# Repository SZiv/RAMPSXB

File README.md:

# RAMPSXB
For anyone who does extensive, hardcore, overkill 3D printer work, will typically run out of either stepper motor slots for extruders, MOSFETS for Heaters/fans, or Thermistor pins. The options for this are to either upgrade to an expensive mainboard like a duet, or add on individial drivers for stepper or FET. There isn't really a cheap or easy option. 

Now there is! RAMPSXB is an expansion board for the popular control board RAMPS 1.4 that connects to the AUX and endstop headers like an arduino shield to add functionality to the system. in addition, most components and schematic layouts follow the Reprap Defacto standard, as well as the original RAMPS board, so the thermistors, FETs, microstepping and drivers should all behave as if they were an extension of the RAMPS board itself. Most components are dirt cheap, and the board can be outsourced and assembled with a simple soldering iron. 

RAMPSXB is an expansion board shield for serious 3D printer people that adds an overkill amount of functionality to run high-end extruder systems like the E3D Kraken or Diamond Full Color Hotend: 

- 4 additional Stepper motors (bringing the total to 9; enough to run 6 extruders) 
- 4 additional Thermistor pins
- 4 additional MOSFETs w/ PWM control
- EXP1 and EXP2 headers for a Reprap Full Graphics Smart Controller (With SD Card)
- 4 additional 12V rail pins w/ grounds
- 4 additional 5V rail pins w/ grounds
- 2 steppers have two rows of output pins for driving 2 motors together
- Broken out, preregulated pins for HC-05 Bluetooth Chip
- Isolated input and microcontroller power, so 12V or 24V power can be used for the FETs. 
- Suppression Capacitors on endstops to reduce false positives caused by inductive voltages.
- 1 servo pin (the other 3 were consumed for PWM on the FETs, but are broken out if you want to use them for something other than the FETS)
- Broken out 12C pins 

This comes at the cost of: 
- 3 of the 4 servo pins. 
- Max endstops (there are only min endstops)
- AAAAAAALL the AUX headers (with the exception of 1 digital pin, D40, which is broken out)
- A lot of additional space

If you have questions, feel free to shoot me a message, or if you want to learn more about the making of this project, see here: http://scottziv.com/rampsxb

Be sure to take a look at the Wiki here: http://reprap.org/wiki/RAMPSXB

Happy printing!

Released under GPL V3

# Pin Definitions

E2 Direction      -  15  
E2 Step           -  19  
E2 Enable         -  63  
E3 Direction      -  2  
E3 Step           -  39  
E3 Enable         -  58  
E4 Direction      -  42  
E4 Step           -  44  
E4 Enable         -  43  
E5 Direction      -  32  
E5 Step           -  47  
E5 Enable         -  57  
Thermistor T3     -  A11  
Thermistor T4     -  A12  
Thermistor T5     -  A10  
Thermistor T6     -  A5  
MOSFET H3          -  4  
MOSFET H4          -  5  
MOSFET H5          -  6  
MOSFET H6          -  45    

HC-05 chip, LCD screen, and SD card follow the standard pinouts for the Full Graphic smart controller and RAMPS HC-05 attachment.

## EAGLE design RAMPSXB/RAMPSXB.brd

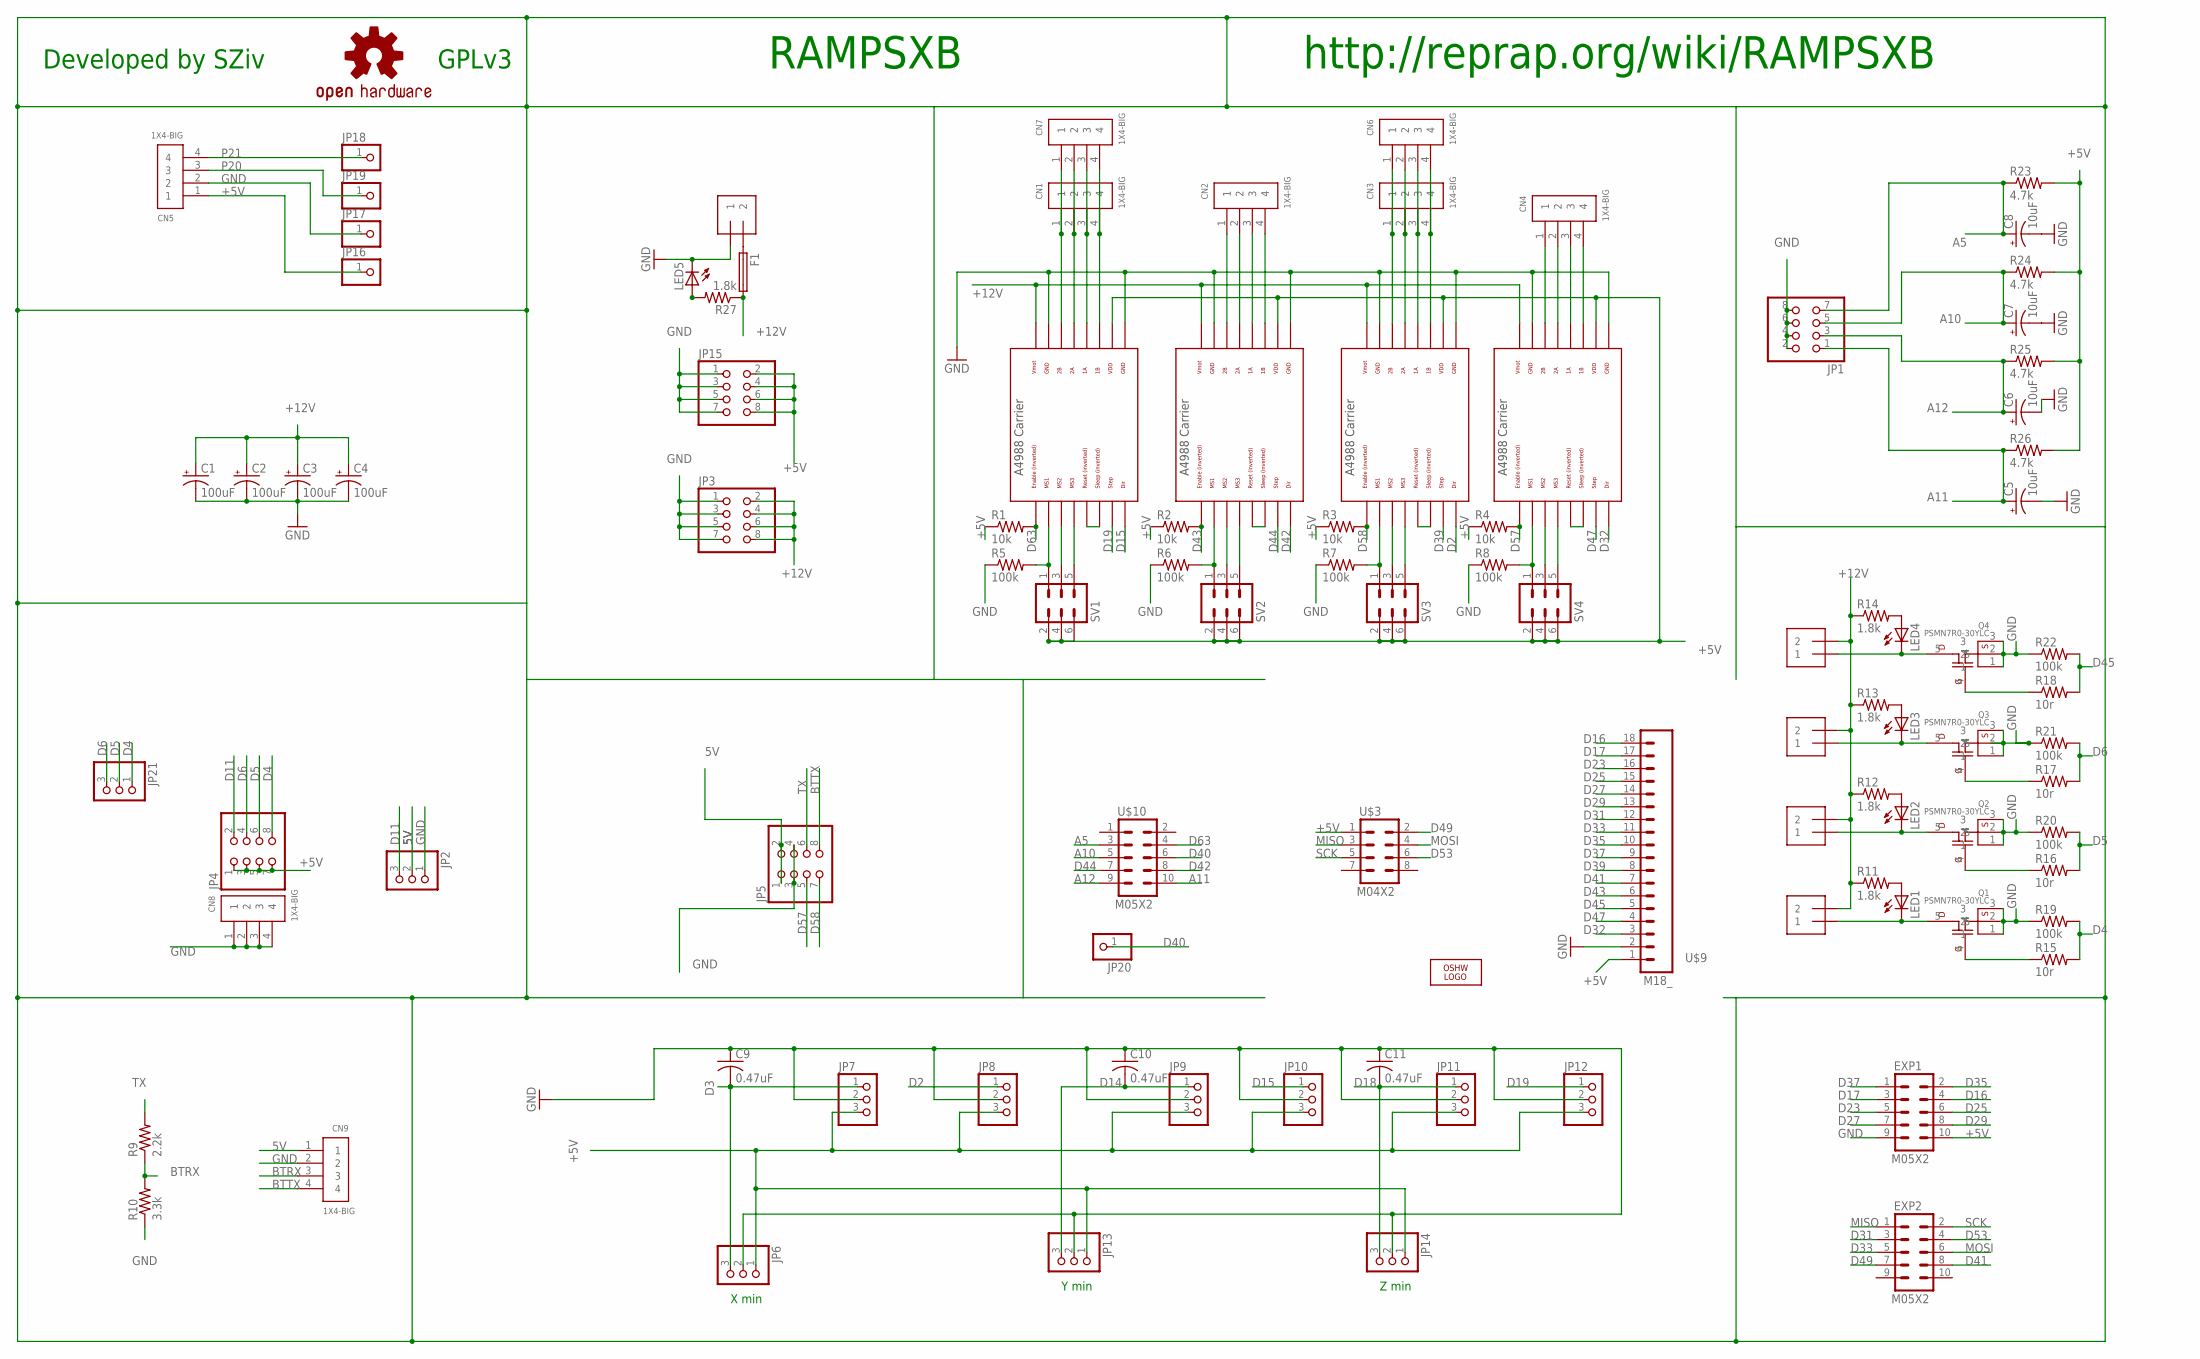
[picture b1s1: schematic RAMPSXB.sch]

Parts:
C1, C2, C3, C4: 100uF; 153CLV-0605
C5, C6, C7, C8: 10uF; 153CLV-0405
C9, C10, C11: 0.47uF; C0805
CN1, CN2, CN3, CN4, CN5, CN6, CN7, CN8, CN9: 1X4-BIG; 1X04-BIG
EXP1, EXP2: M05X2; 2X5
F1: PTCFUSE; LITTLEFUSE
J1, J2, J3, J4, J5: 1X2-3.5MM
JP1, JP3, JP4, JP5, JP15: PINHD-2X4; 2X04
JP2, JP6, JP7, JP8, JP9, JP10, JP11, JP12, JP13, JP14, JP21: PINHD-1X3; 1X03
JP16, JP17, JP18, JP19, JP20: PINHD-1X1; 1X01
LED1, LED2, LED3, LED4, LED5: LEDCHIPLED_0805; CHIPLED_0805
LOGO1: OSHW_LOGO_6MILX0100-NT; OSHW_6X100_NOTEXT
LOGO2: OSHW-LOGOL; OSHW-LOGO-L
Q1, Q2, Q3, Q4: PSMN7R0-30YLC; LFPAK
R1, R2, R3, R4: 10k; M0805
R5, R6, R7, R8, R19, R20, R21, R22: 100k; M0805
R9: 2.2k; M0805
R10: 3.3k; M0805
R11, R12, R13, R14, R27: 1.8k; M0805
R15, R16, R17, R18: 10r; M0805
R23, R24, R25, R26: 4.7k; R0805
SV1, SV2, SV3, SV4: MA03-2
U$1, U$2, U$4, U$5: POLOLU_A4983CARRIER; A4988BREAKOUT
U$3: M04X2; 2X4
U$9: M18_; 1X18
U$10: M05X2; 2X5

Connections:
5V: CN9.1, JP2.2, JP5.1, JP5.2
+5V: CN5.1, EXP1.10, JP4.1, JP4.3, JP4.5, JP4.7, JP6.1, JP7.3, JP8.3, JP9.3, JP10.3, JP11.3, JP12.3, JP13.1, JP14.1, JP15.2, JP15.4, JP15.6, JP15.8, JP16.1, R1.1, R2.1, R3.1, R4.1, R23.2, R24.2, R25.2, R26.2, SV1.2, SV1.4, SV1.6, SV2.2, SV2.4, SV2.6, SV3.2, SV3.4, SV3.6, SV4.2, SV4.4, SV4.6, U$1.VDD, U$2.VDD, U$3.1, U$4.VDD, U$5.VDD, U$9.1
+12V: C1.+, C2.+, C3.+, C4.+, F1.2, J2.2, J3.2, J4.2, J5.2, JP3.2, JP3.4, JP3.6, JP3.8, R11.1, R12.1, R13.1, R14.1, R27.1, U$1.VMOT, U$2.VMOT, U$4.VMOT, U$5.VMOT
A5: C8.+, JP1.7, R23.1, U$10.3
A10: C7.+, JP1.5, R24.1, U$10.5
A11: C5.+, JP1.1, R26.1, U$10.10
A12: C6.+, JP1.3, R25.1, U$10.9
BTRX: CN9.3, R9.1, R10.2
BTTX: CN9.4, JP5.8
D2: JP8.1, U$4.DIR
D3: C9.2, JP6.3, JP7.1
D4: JP4.8, JP21.1, R15.2, R19.2
D5: JP4.6, JP21.2, R16.2, R20.2
D6: JP4.4, JP21.3, R17.2, R21.2
D11: JP2.3, JP4.2
D14: C10.2, JP9.1, JP13.3
D15: JP10.1, U$1.DIR
D16: EXP1.4, U$9.18
D17: EXP1.3, U$9.17
D18: C11.2, JP11.1, JP14.3
D19: JP12.1, U$1.STEP
D23: EXP1.5, U$9.16
D25: EXP1.6, U$9.15
D27: EXP1.7, U$9.14
D29: EXP1.8, U$9.13
D31: EXP2.3, U$9.12
D32: U$5.DIR, U$9.3
D33: EXP2.5, U$9.11
D35: EXP1.2, U$9.10
D37: EXP1.1, U$9.9
D39: U$4.STEP, U$9.8
D40: JP20.1, U$10.6
D41: EXP2.8, U$9.7
D42: U$2.DIR, U$10.8
D43: R2.2, U$2.EN, U$9.6
D44: U$2.STEP, U$10.7
D45: R18.2, R22.2, U$9.5
D47: U$5.STEP, U$9.4
D49: EXP2.7, U$3.2
D53: EXP2.4, U$3.6
D57: JP5.5, R4.2, U$5.EN
D58: JP5.7, R3.2, U$4.EN
D63: R1.2, U$1.EN, U$10.4
GND: C1.-, C2.-, C3.-, C4.-, C5.-, C6.-, C7.-, C8.-, C9.1, C10.1, C11.1, CN5.2, CN8.1, CN8.2, CN8.3, CN8.4, CN9.2, EXP1.9, J1.1, JP1.2, JP1.4, JP1.6, JP1.8, JP2.1, JP3.1, JP3.3, JP3.5, JP3.7, JP5.3, JP5.4, JP6.2, JP7.2, JP8.2, JP9.2, JP10.2, JP11.2, JP12.2, JP13.2, JP14.2, JP15.1, JP15.3, JP15.5, JP15.7, JP17.1, LED5.C, Q1.1, Q1.2, Q1.3, Q2.1, Q2.2, Q2.3, Q3.1, Q3.2, Q3.3, Q4.1, Q4.2, Q4.3, R5.1, R6.1, R7.1, R8.1, R10.1, R19.1, R20.1, R21.1, R22.1, U$1.GND, U$1.GND@0 (GND), U$2.GND, U$2.GND@0 (GND), U$4.GND, U$4.GND@0 (GND), U$5.GND, U$5.GND@0 (GND), U$9.2
MISO: EXP2.1, U$3.3
MOSI: EXP2.6, U$3.4
unnamed: CN1.1, CN7.1, U$1.2B
unnamed: LED5.A, R27.2
unnamed: CN1.3, CN7.3, U$1.1A
unnamed: CN1.4, CN7.4, U$1.1B
unnamed: CN2.1, U$2.2B
unnamed: CN2.2, U$2.2A
unnamed: CN2.3, U$2.1A
unnamed: CN2.4, U$2.1B
unnamed: CN3.1, CN6.1, U$4.2B
unnamed: CN3.2, CN6.2, U$4.2A
unnamed: CN3.3, CN6.3, U$4.1A
unnamed: CN3.4, CN6.4, U$4.1B
unnamed: CN4.1, U$5.2B
unnamed: CN4.2, U$5.2A
unnamed: CN4.3, U$5.1A
unnamed: CN4.4, U$5.1B
unnamed: F1.1, J1.2
unnamed: R5.2, SV1.1, U$1.MS1
unnamed: SV1.3, U$1.MS2
unnamed: SV1.5, U$1.MS3
unnamed: R6.2, SV2.1, U$2.MS1
unnamed: SV2.3, U$2.MS2
unnamed: SV2.5, U$2.MS3
unnamed: R7.2, SV3.1, U$4.MS1
unnamed: SV3.3, U$4.MS2
unnamed: SV3.5, U$4.MS3
unnamed: R8.2, SV4.1, U$5.MS1
unnamed: SV4.3, U$5.MS2
unnamed: SV4.5, U$5.MS3
unnamed: J2.1, LED1.C, Q1.5
unnamed: U$2.RST, U$2.SLP (SLEEP)
unnamed: U$1.RST, U$1.SLP (SLEEP)
unnamed: U$4.RST, U$4.SLP (SLEEP)
unnamed: U$5.RST, U$5.SLP (SLEEP)
unnamed: J3.1, LED2.C, Q2.5
unnamed: J4.1, LED3.C, Q3.5
unnamed: J5.1, LED4.C, Q4.5
unnamed: LED1.A, R11.2
unnamed: LED2.A, R12.2
unnamed: LED3.A, R13.2
unnamed: LED4.A, R14.2
unnamed: CN1.2, CN7.2, U$1.2A
unnamed: Q3.4, R17.1
unnamed: Q4.4, R18.1
unnamed: Q2.4, R16.1
unnamed: Q1.4, R15.1
P20: CN5.3, JP19.1
P21: CN5.4, JP18.1
SCK: EXP2.2, U$3.5
TX: JP5.6, R9.2

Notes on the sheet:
X min
Y min
Z min
RAMPSXB
http://reprap.org/wiki/RAMPSXB
Developed by SZiv
GPLv3

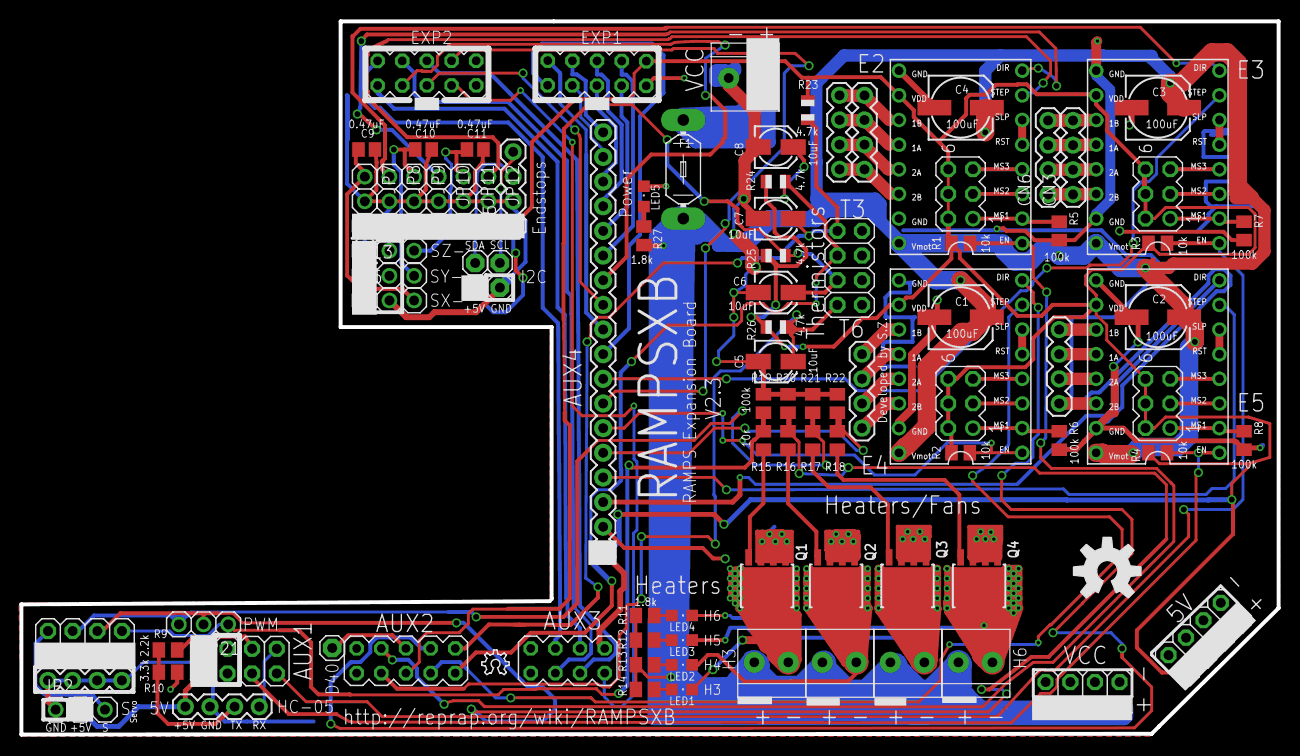
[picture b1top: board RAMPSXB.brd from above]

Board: 2 copper layers, 129.5 x 73.5 mm, 98 parts (0 on the bottom side), 96 nets.

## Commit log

2017-07-25 :boom::camel: Added .gitattributes & .gitignore files
2017-07-25 Main Commit
    First Commit
2017-07-25 Readme Added
    Adding Readme
2017-07-27 V2!
    V2 release. Full PWM, Bluetooth, Larger board.
2017-07-27 Seperated out BOM
2017-08-05 Removed Old RAMPS version.
    SD card slot did not have logic level shifter, so it would fry SD cards
    inserted into it. Whoops.
    Removed all files so people wouldnt accidently make it
2017-08-08 Rerouting, broken out PWM pins
    Rerouting, broken out PWM pins
2017-08-23 Reroute
    Reroute of some wires
2017-08-23 Exposed Power Traces
    Exposed Traces to increase current by covering with solder
2017-08-24 Updated BOM. Dont know what happened.
2017-08-26 Added Power Indicator and fixed a short.
    Added Power indicator LED, and Fixed a major issue where +5V on the
    arduino was connected to ground. Whoops.
2017-08-28 Added Gerber Files. Slight Rewiring.
    Added Gerber Files for production run. Fixed some clearance issues.
2017-08-28 Swapped pins 49 and 43. Documentation for the Smart Controller was incorrect.
    Almost everything works, but the SD card for some reason opens, but I
    cant read anything. Still working on that.
2017-08-28 Fixed the SD card issue. I wasn't wiring it right. ¯\_(ツ)_/¯
    No changes.
2017-08-29 Replaced FETs with PSMN7R0-30YLCs for production.
    Added Older Version Directory for the old STP55 board. It should also
    work as well.
2017-09-07 Expanded the traces on the FETs, corrected some incorrect pins on the infographic.
2017-09-25 Fixed LED Numbering, updated V2.1
    LED Indicators were not on the right FETs. Not sure how I missed that.
    Updated V2.1 with corrected Vector Text.
2017-09-25 Expanded Traces, Fixed Fonts
    Changed Fonts to Vector, so they come out in the right place. Expanded
    power traces.
2017-09-26 Fixed Incorrect label
    Incorrect Label on Pin listing. Had 2 D32s. Corrected to D42.
2017-09-26 Added Labeling for the Heater LEDs.
    So you know which one is which
2017-09-26 Updated Gerbers, Added the firmware
    Updated Gerbers and added a working firmware. The firmware is for a
    full-on 6 extruder mess using a Full Graphics Smart Controller. Unless
    you happen to have the same setup I do, You should go to the Repetier
    Firmware configurator and adapt it to your needs.
2017-09-26 Incremented Version number and added a bigger OSHW Logo to fill in the empty space
    Hopefully, this should be close to the final version
2017-09-26 Fixed some issues with V2.1, and updated gerbers
    fixed some stuff with V2.1 and corrected some issues
2017-09-27 Labeling for R9 and R10 was flipped. Fixed.
2017-11-05 Minor Fixes
    Did some separation between the power leads because they are really
    close.
    Cleaned up the Silkscreen a little bit, and labeled servo pins.
2018-05-08 flipped Min X and Min Z pin labeling
    Corrected an error where the labeling for the Min Z and Min X pins were
    flipped. Not sure how I missed that one!

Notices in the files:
parts and their libraries:
SparkFun-Aesthetics: Licensing: Creative Commons ShareAlike 4.0 International - https://creativecommons.org/licenses/by-sa/4.0
MyLibrary: Copyright (C) 2008, Bob Starr
